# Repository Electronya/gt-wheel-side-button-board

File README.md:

# gt-wheel-side-button-board
GT Wheel Side Buttons Board

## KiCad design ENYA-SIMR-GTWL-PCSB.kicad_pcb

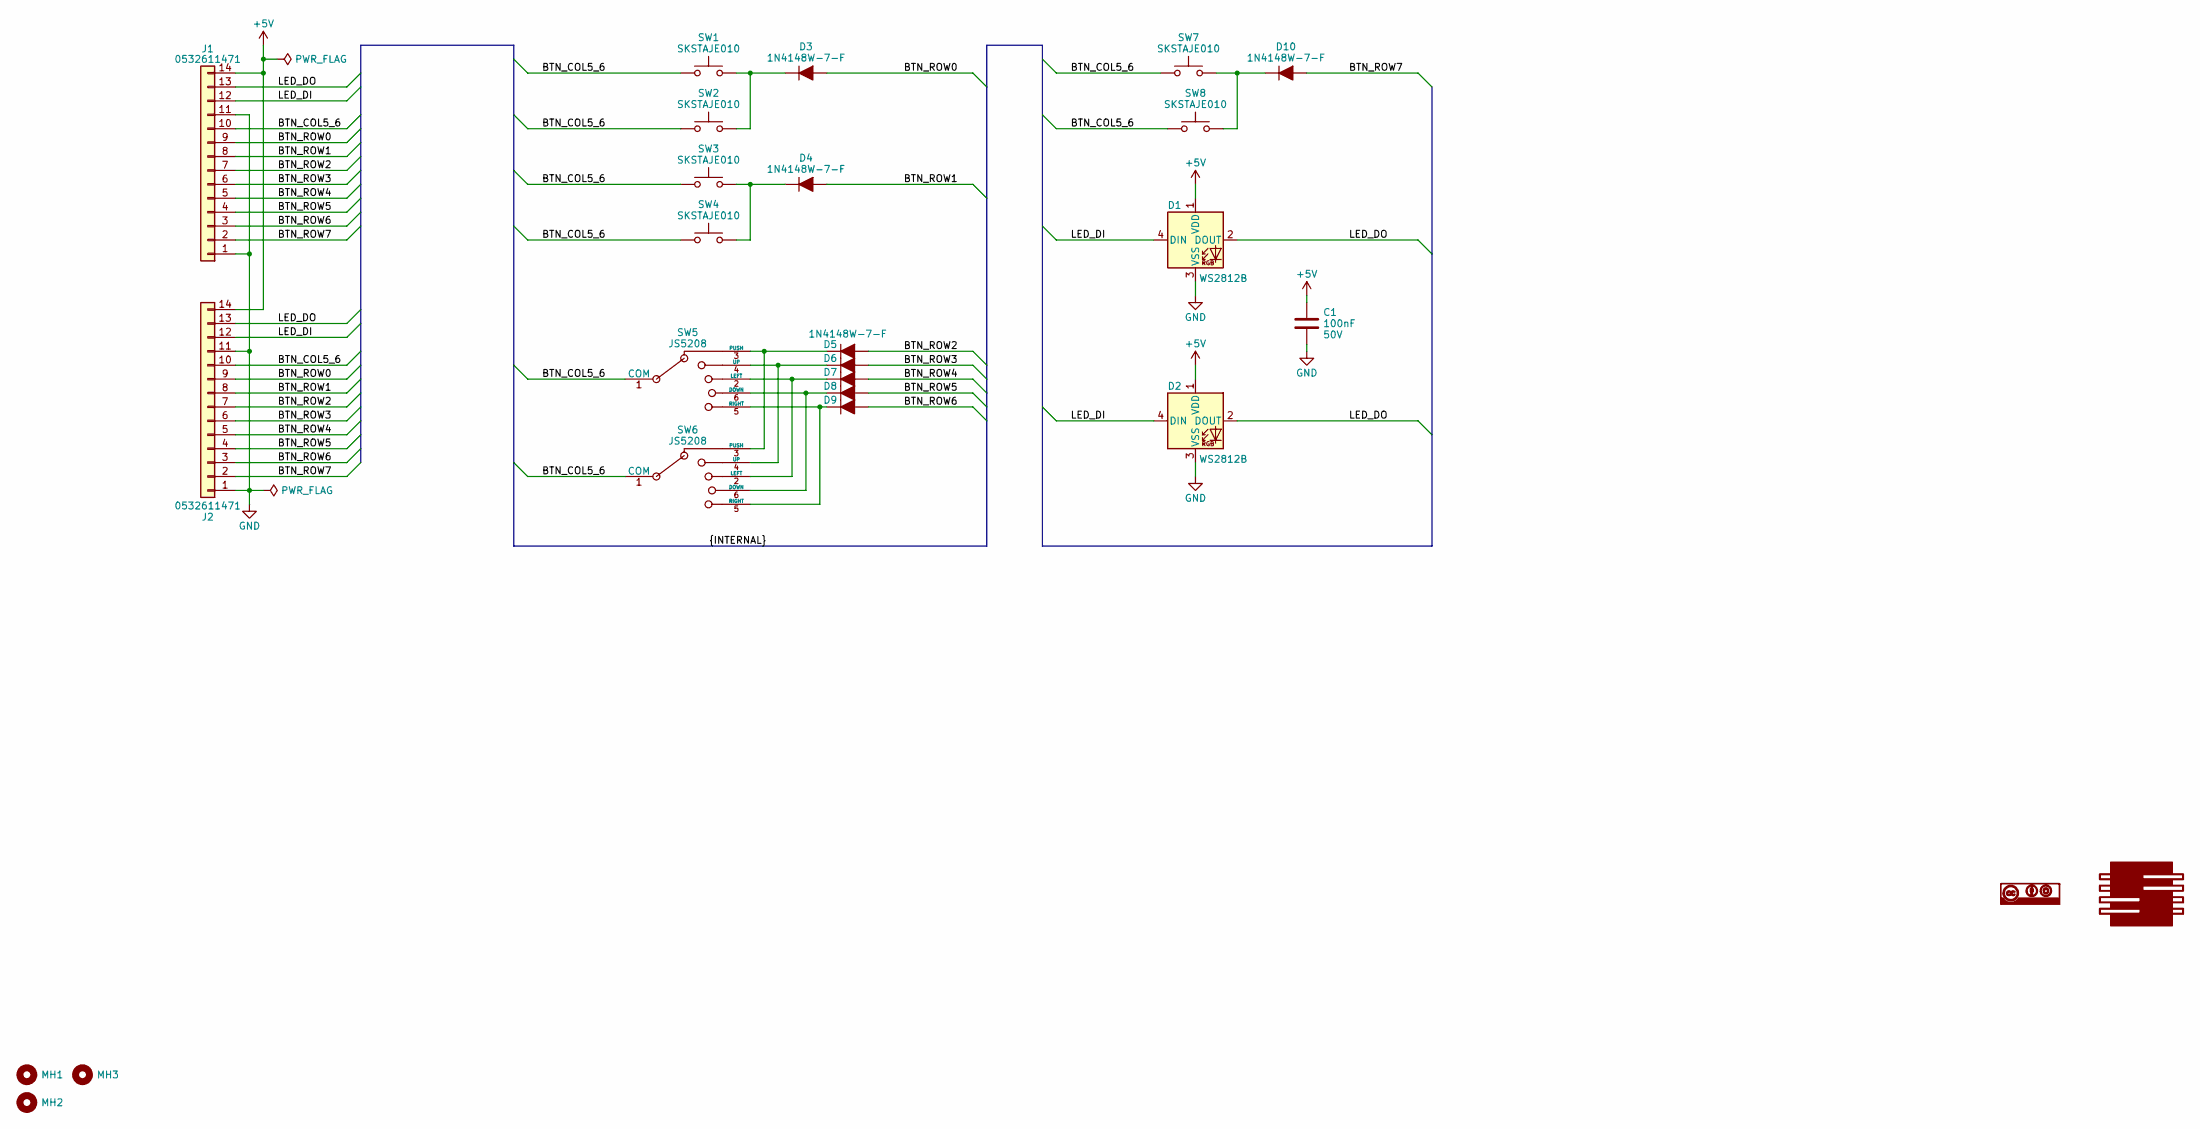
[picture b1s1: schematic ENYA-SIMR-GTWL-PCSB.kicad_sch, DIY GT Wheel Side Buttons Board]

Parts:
C1: 100nF_CER_0603_50V; C_0603_1608Metric; Voltage Rating 50V; Manufacturer Part Number 06033D104MAT2A; Digi-Key Part Number 478-7905-1-ND
D1, D2: WS2812B; LED_WS2812B_PLCC4_5.0x5.0mm_P3.2mm; Manaufacturer Part Numb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 4684; Digi-Key Part Number 1528-4684-ND
D3, D4, D5, D6, D7, D8, D9, D10: 1N4148W-7-F; D_SOD-123; Manufacturer Part Number 1N4148W-7-F; Digi-Key Part Number 1N4148W-FDICT-ND
G1: Electronya_Logo; Electronya_Logo_12MM
G2: CC-BY-SA_Logo; CC-BY-SA_12MM
J1, J2: PICO_BLADE_1x14_MALE_RA_SMD; PICO_BLADE_53261_1x14_SMD_RA_1.25MM; Manufacturer Part Number 0532611471; Digi-Key Part Number WM7631CT-ND
MH1, MH2, MH3: MH-NPLTD-M3; MountingHole_3.2mm_M3_DIN965
SW1, SW2, SW3, SW4, SW7, SW8: SKSTAJE010; SKSTAJE_Alps_SPST; Manufacturer Part Number SKSTAJE010; Mouser Part Number 688-SKSTAJE010
SW5, SW6: JS5208; JS5208_4_DIR_1_PUSH; Manufacturer PArt Number JS5208; Digi-Key Part Number EG4561-ND

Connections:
+5V: C1.1, D1.1 (VDD), D2.1 (VDD), J1.14, J2.14
/BTN_COL5_6: J1.10, J2.10, SW1.1, SW2.1, SW3.1, SW4.1, SW5.1 (COM), SW6.1 (COM), SW7.1, SW8.1
/BTN_ROW0: D3.2 (A), J1.9, J2.9
/BTN_ROW1: D4.2 (A), J1.8, J2.8
/BTN_ROW2: D5.2 (A), J1.7, J2.7
/BTN_ROW3: D6.2 (A), J1.6, J2.6
/BTN_ROW4: D7.2 (A), J1.5, J2.5
/BTN_ROW5: D8.2 (A), J1.4, J2.4
/BTN_ROW6: D9.2 (A), J1.3, J2.3
/BTN_ROW7: D10.2 (A), J1.2, J2.2
/LED_DI: D1.4 (DIN), D2.4 (DIN), J1.12, J2.12
/LED_DO: D1.2 (DOUT), D2.2 (DOUT), J1.13, J2.13
GND: C1.2, D1.3 (VSS), D2.3 (VSS), J1.1, J1.11, J2.1, J2.11
unnamed: D3.1 (K), SW1.2, SW2.2
unnamed: D4.1 (K), SW3.2, SW4.2
unnamed: D5.1 (K), SW5.3 (PUSH), SW6.3 (PUSH)
unnamed: D6.1 (K), SW5.4 (UP), SW6.4 (UP)
unnamed: D7.1 (K), SW5.2 (LEFT), SW6.2 (LEFT)
unnamed: D8.1 (K), SW5.6 (DOWN), SW6.6 (DOWN)
unnamed: D9.1 (K), SW5.5 (RIGHT), SW6.5 (RIGHT)
unnamed: D10.1 (K), SW7.2, SW8.2

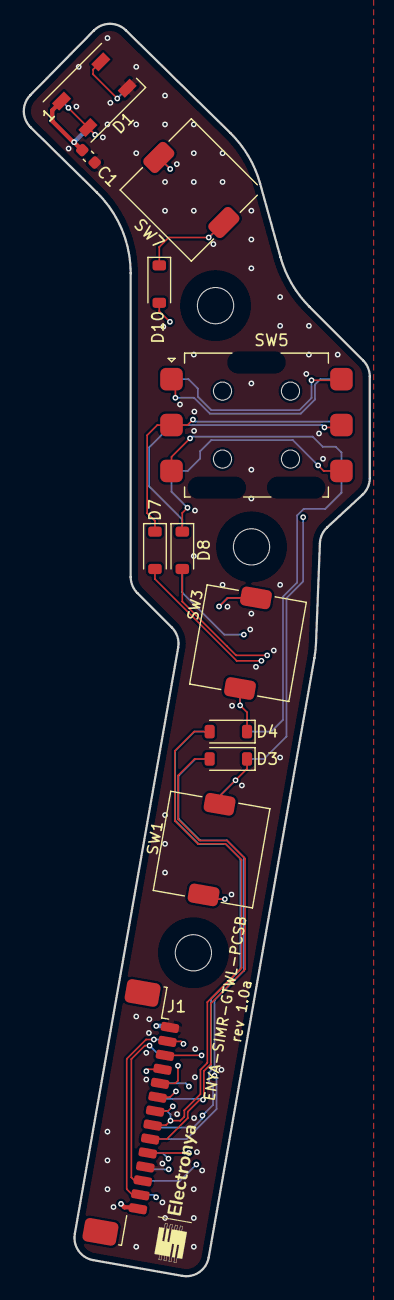
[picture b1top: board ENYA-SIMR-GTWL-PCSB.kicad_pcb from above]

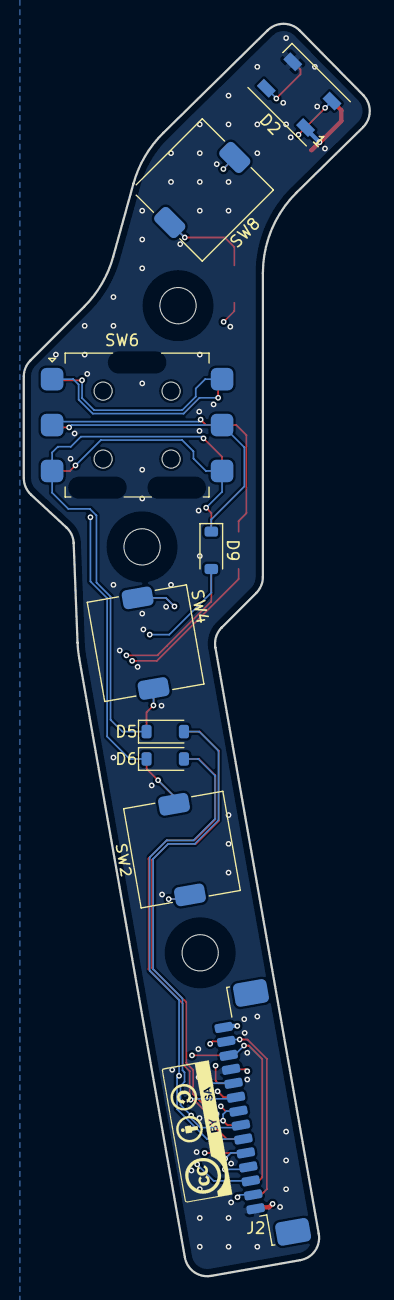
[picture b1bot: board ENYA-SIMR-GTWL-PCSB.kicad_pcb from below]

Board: 4 copper layers, 30.5 x 110.5 mm, 26 parts (10 on the bottom side), 21 nets.

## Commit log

2023-06-30 routing done, ready for tag
2023-06-30 updating gitignore + adding left and right step files
2023-06-30 adding LED decoupling cap
2023-07-01 correction button matrix diode polarity
2023-07-01 drill origin

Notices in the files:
parts and their libraries:
CC-BY-SA, creative common
